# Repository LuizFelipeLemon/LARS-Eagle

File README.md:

View this project on [CADLAB.io](https://cadlab.io/project/1295). 

# LARS-Eagle
oi

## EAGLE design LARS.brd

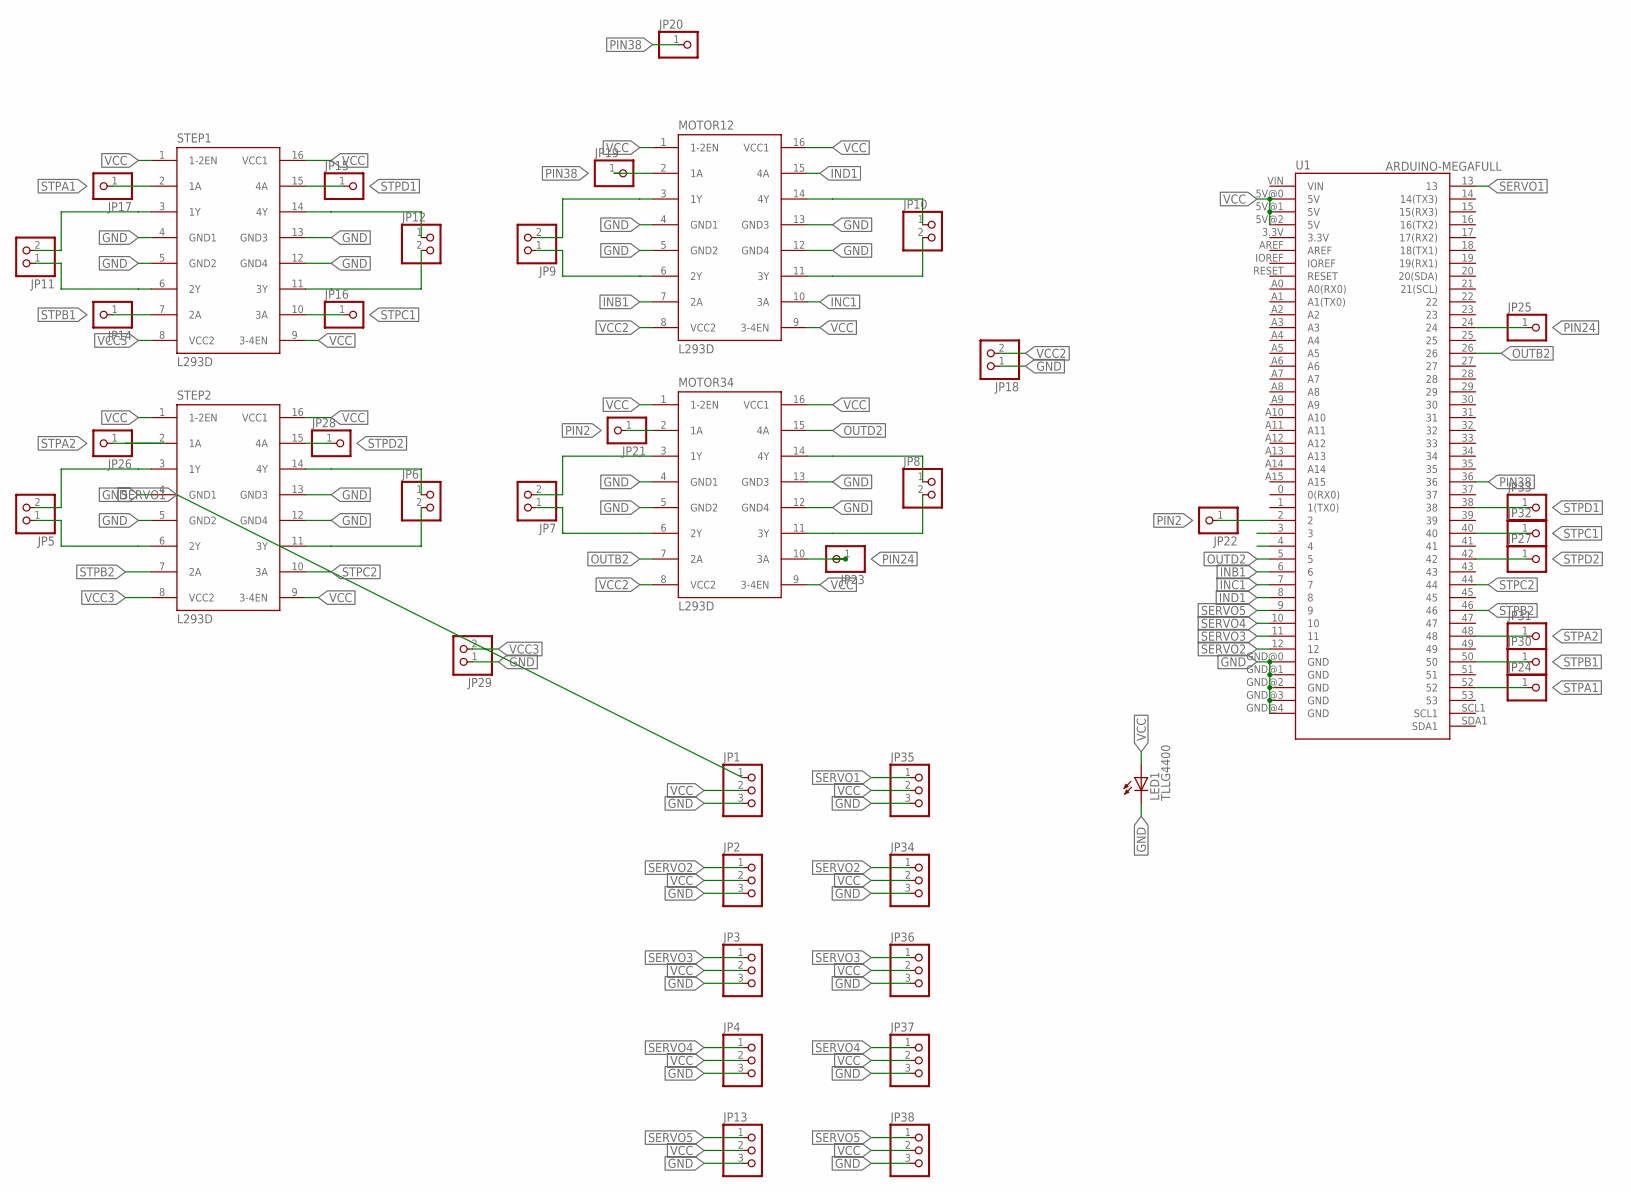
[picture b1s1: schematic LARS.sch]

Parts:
JP1, JP2, JP3, JP4, JP13, JP34, JP35, JP36, JP37, JP38: PINHD-1X3; 1X03
JP5, JP6, JP7, JP8, JP9, JP10, JP11, JP12, JP18, JP29: PINHD-1X2; 1X02
JP14, JP15, JP16, JP17, JP19, JP20, JP21, JP22, JP23, JP24, JP25, JP26, JP27, JP28, JP30, JP31, JP32, JP33: PINHD-1X1; 1X01
LED1: TLLG4400; LED3MM
MOTOR12, MOTOR34: L293D; DIL16
STEP1, STEP2: L293D; DIL16
U1: ARDUINO-MEGAFULL; ARDUINO_MEGA

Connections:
GND: JP1.3, JP2.3, JP3.3, JP4.3, JP13.3, JP18.1, JP29.1, JP34.3, JP35.3, JP36.3, JP37.3, JP38.3, LED1.K (C), MOTOR12.4 (GND1), MOTOR12.5 (GND2), MOTOR12.12 (GND4), MOTOR12.13 (GND3), MOTOR34.4 (GND1), MOTOR34.5 (GND2), MOTOR34.12 (GND4), MOTOR34.13 (GND3), STEP1.4 (GND1), STEP1.5 (GND2), STEP1.12 (GND4), STEP1.13 (GND3), STEP2.4 (GND1), STEP2.5 (GND2), STEP2.12 (GND4), STEP2.13 (GND3), U1.GND@0 (GND), U1.GND@1 (GND), U1.GND@2 (GND), U1.GND@3 (GND), U1.GND@4 (GND)
INB1: MOTOR12.7 (2A), U1.6
INC1: MOTOR12.10 (3A), U1.7
IND1: MOTOR12.15 (4A), U1.8
OUTB2: MOTOR34.7 (2A), U1.26
OUTD2: MOTOR34.15 (4A), U1.5
PIN2: JP21.1, JP22.1, MOTOR34.2 (1A), U1.2
PIN24: JP23.1, JP25.1, MOTOR34.10 (3A), U1.24
PIN38: JP19.1, JP20.1, MOTOR12.2 (1A), U1.36
SERVO1: JP1.1, JP35.1, U1.13
SERVO2: JP2.1, JP34.1, U1.12
SERVO3: JP3.1, JP36.1, U1.11
SERVO4: JP4.1, JP37.1, U1.10
SERVO5: JP13.1, JP38.1, U1.9
STP1: JP5.2, STEP2.3 (1Y)
STP2: JP5.1, STEP2.6 (2Y)
STP3: JP6.2, STEP2.11 (3Y)
STP4: JP6.1, STEP2.14 (4Y)
STP5: JP7.2, MOTOR34.3 (1Y)
STP6: JP7.1, MOTOR34.6 (2Y)
STP7: JP8.2, MOTOR34.11 (3Y)
STP8: JP8.1, MOTOR34.14 (4Y)
STP9: JP9.2, MOTOR12.3 (1Y)
STP10: JP9.1, MOTOR12.6 (2Y)
STP11: JP10.2, MOTOR12.11 (3Y)
STP12: JP10.1, MOTOR12.14 (4Y)
STP13: JP11.2, STEP1.3 (1Y)
STP14: JP11.1, STEP1.6 (2Y)
STP15: JP12.2, STEP1.11 (3Y)
STP16: JP12.1, STEP1.14 (4Y)
STPA1: JP17.1, JP24.1, STEP1.2 (1A), U1.52
STPA2: JP26.1, JP31.1, STEP2.2 (1A), U1.48
STPB1: JP14.1, JP30.1, STEP1.7 (2A), U1.50
STPB2: STEP2.7 (2A), U1.46
STPC1: JP16.1, JP32.1, STEP1.10 (3A), U1.40
STPC2: STEP2.10 (3A), U1.44
STPD1: JP15.1, JP33.1, STEP1.15 (4A), U1.38
STPD2: JP27.1, JP28.1, STEP2.15 (4A), U1.42
VCC: JP1.2, JP2.2, JP3.2, JP4.2, JP13.2, JP34.2, JP35.2, JP36.2, JP37.2, JP38.2, LED1.A, MOTOR12.1 (1-2EN), MOTOR12.9 (3-4EN), MOTOR12.16 (VCC1), MOTOR34.1 (1-2EN), MOTOR34.9 (3-4EN), MOTOR34.16 (VCC1), STEP1.1 (1-2EN), STEP1.9 (3-4EN), STEP1.16 (VCC1), STEP2.1 (1-2EN), STEP2.9 (3-4EN), STEP2.16 (VCC1), U1.5V@0 (5V), U1.5V@1 (5V), U1.5V@2 (5V)
VCC2: JP18.2, MOTOR12.8 (VCC2), MOTOR34.8 (VCC2)
VCC3: JP29.2, STEP1.8 (VCC2), STEP2.8 (VCC2)

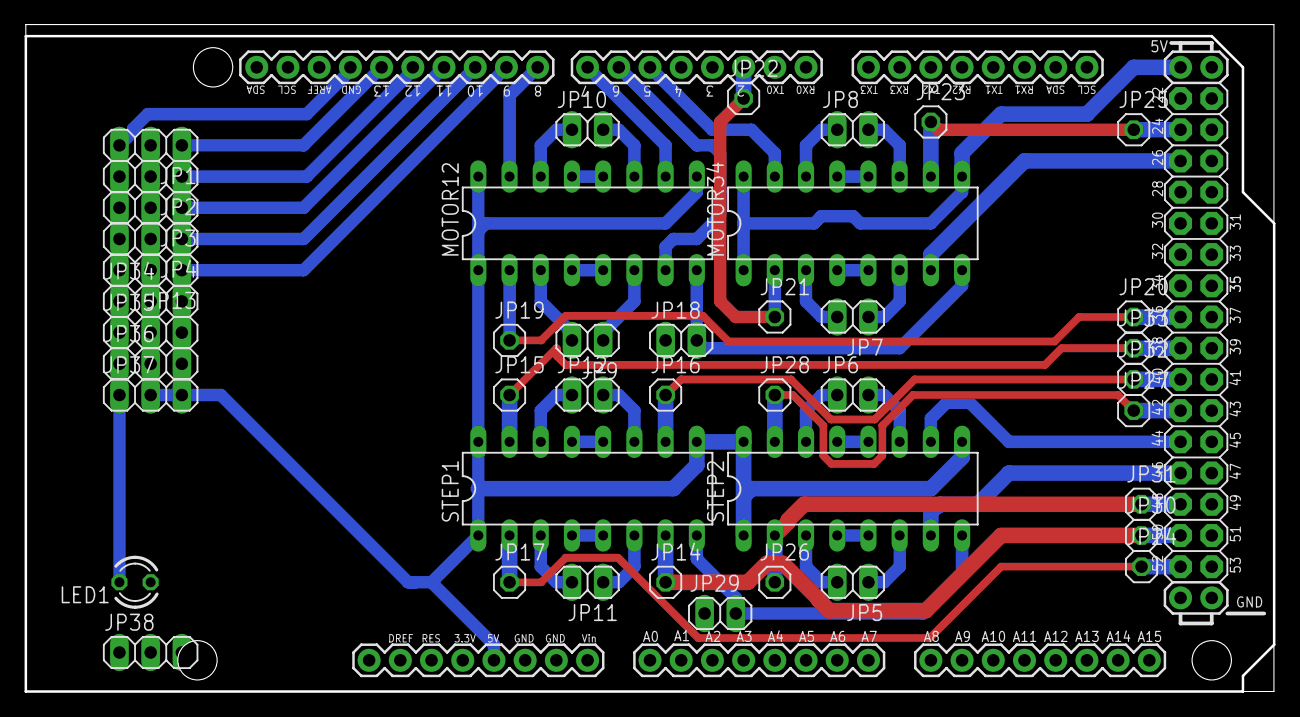
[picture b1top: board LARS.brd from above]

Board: 2 copper layers, 101.6 x 54.2 mm, 44 parts (0 on the bottom side), 41 nets.

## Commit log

2018-09-12 placa dia 12/09
2018-09-14 parei de mexer na placa pra tentar fazer o robô móvel
2018-09-14 Backlink to CADLAB.io has been added.
